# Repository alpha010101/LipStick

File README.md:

人感センサー（Panasonic EKMC1601111)を筐体に実装するための補助基板。筐体内での他の信号線などの中継機能を含む。

SchematicとPCB-LayoutをAutodesk-Eagle無償版で作成し、elecrowで製造することを前提にガーバーを作成

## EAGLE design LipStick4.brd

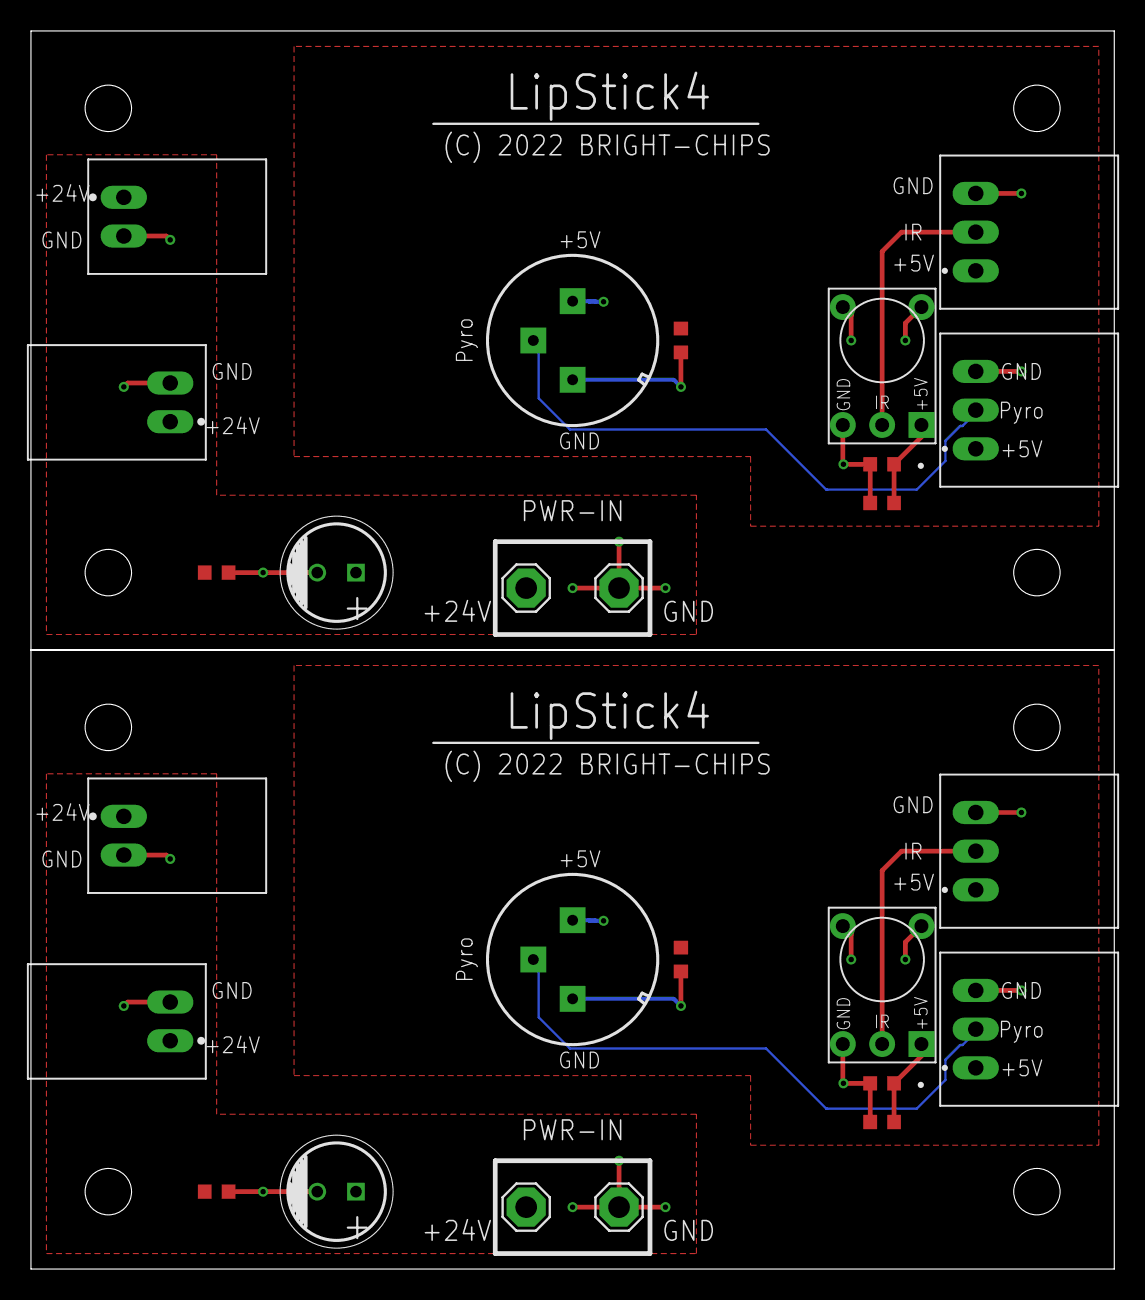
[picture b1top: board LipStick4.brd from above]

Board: 2 copper layers, 70.0 x 80.0 mm, 26 parts (0 on the bottom side), 10 nets.

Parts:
C1, C2, C3, C4, C5, C6, C7, C8: GRM188R71H104KA93D; CAPC1608X90N
CE1, CE2: ECA-1HM470I; CAPPRD250W55D630H1220
J1, J2, J3, J4: S3B-XH-A(LF)(SN); JST_S3B-XH-A(LF)(SN)
J5, J6: SPS-442
LSP1, LSP2, LSP3, LSP4: SE14
P1, P2, P3, P4: S2B-XH-A(LF)(SN); JST_S2B-XH-A(LF)(SN)
PH1, PH2: EKMC1601111; VZ-STANDARD

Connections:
+5V: C1.2, C3.1, C4.1, J2.1, J4.1, J5.1, PH1.3
+5V1: C6.2, C7.1, C8.1, J1.1, J3.1, J6.1, PH2.3
+24V: C2.2, CE1.1, LSP1.MP, P2.1, P3.1
+24V1: C5.2, CE2.1, LSP3.MP, P1.1, P4.1
GND: C1.1, C2.1, C3.2, C4.2, CE1.2, J2.3, J4.3, J5.3, J5.4, J5.5, LSP2.MP, P2.2, P3.2, PH1.1
GND1: C5.1, C6.1, C7.2, C8.2, CE2.2, J1.3, J3.3, J6.3, J6.4, J6.5, LSP4.MP, P1.2, P4.2, PH2.1
IR: J4.2, J5.2
IR1: J3.2, J6.2
PYRO: J2.2, PH1.2
PYRO1: J1.2, PH2.2

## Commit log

2025-01-01 initial release

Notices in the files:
LipStick4.brd:
(C) 2022 BRIGHT-CHIPS
